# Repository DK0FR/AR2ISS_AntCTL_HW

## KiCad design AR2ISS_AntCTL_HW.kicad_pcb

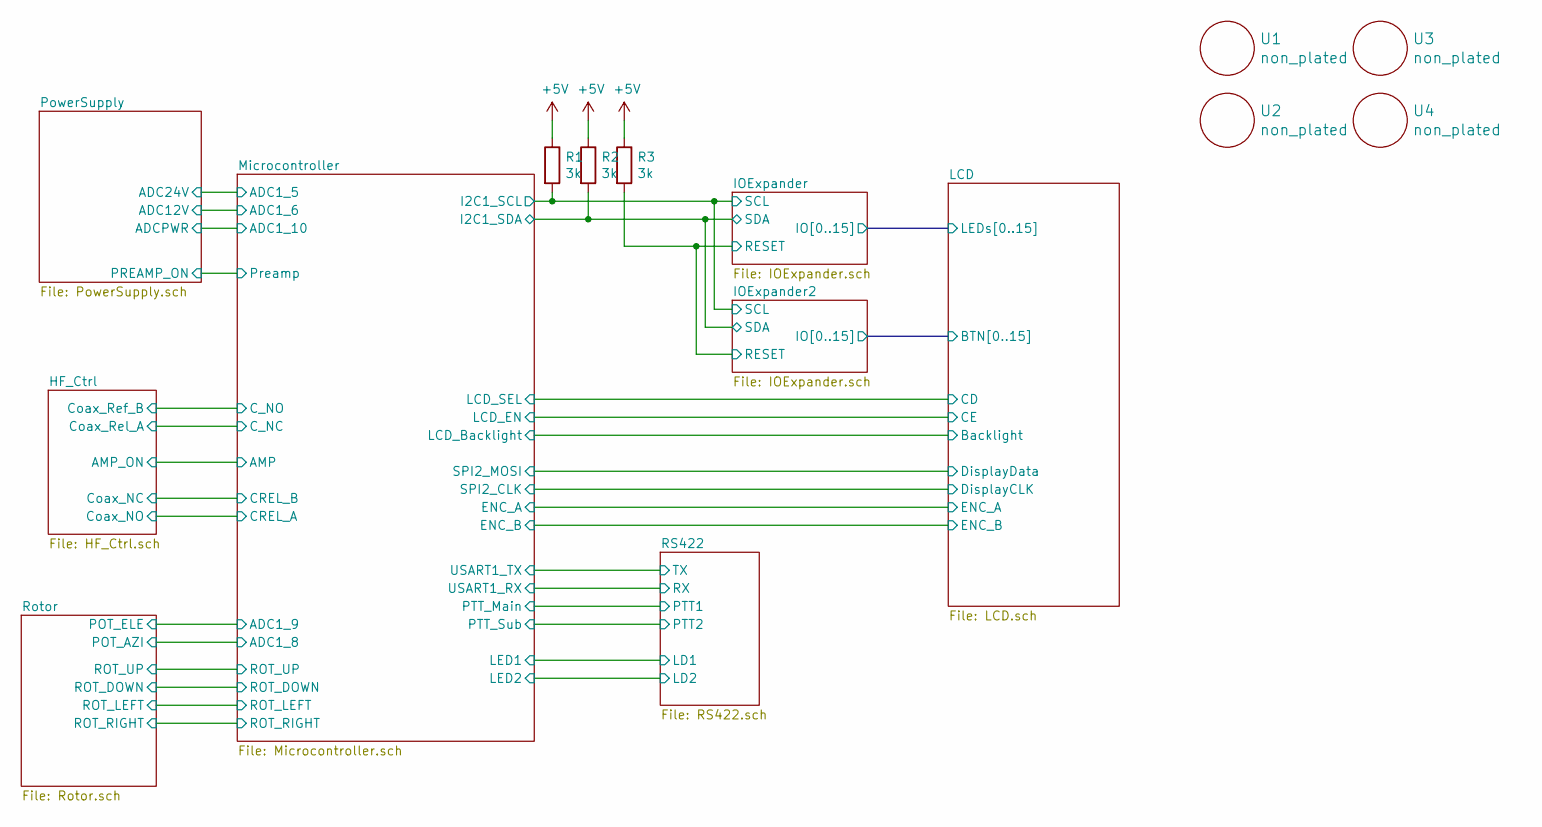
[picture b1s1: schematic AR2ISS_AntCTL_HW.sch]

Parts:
R1, R2, R3: 3k; R_0603_1608Metric
U1, U2, U3, U4: non_plated; non_plated_3mm

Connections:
+5V: R1.1, R2.1, R3.1; also elsewhere on the board
/IOExpander/RESET: R3.2; also elsewhere on the board
/Microcontroller/I2C1_SCL: R1.2; also elsewhere on the board
/Microcontroller/I2C1_SDA: R2.2; also elsewhere on the board

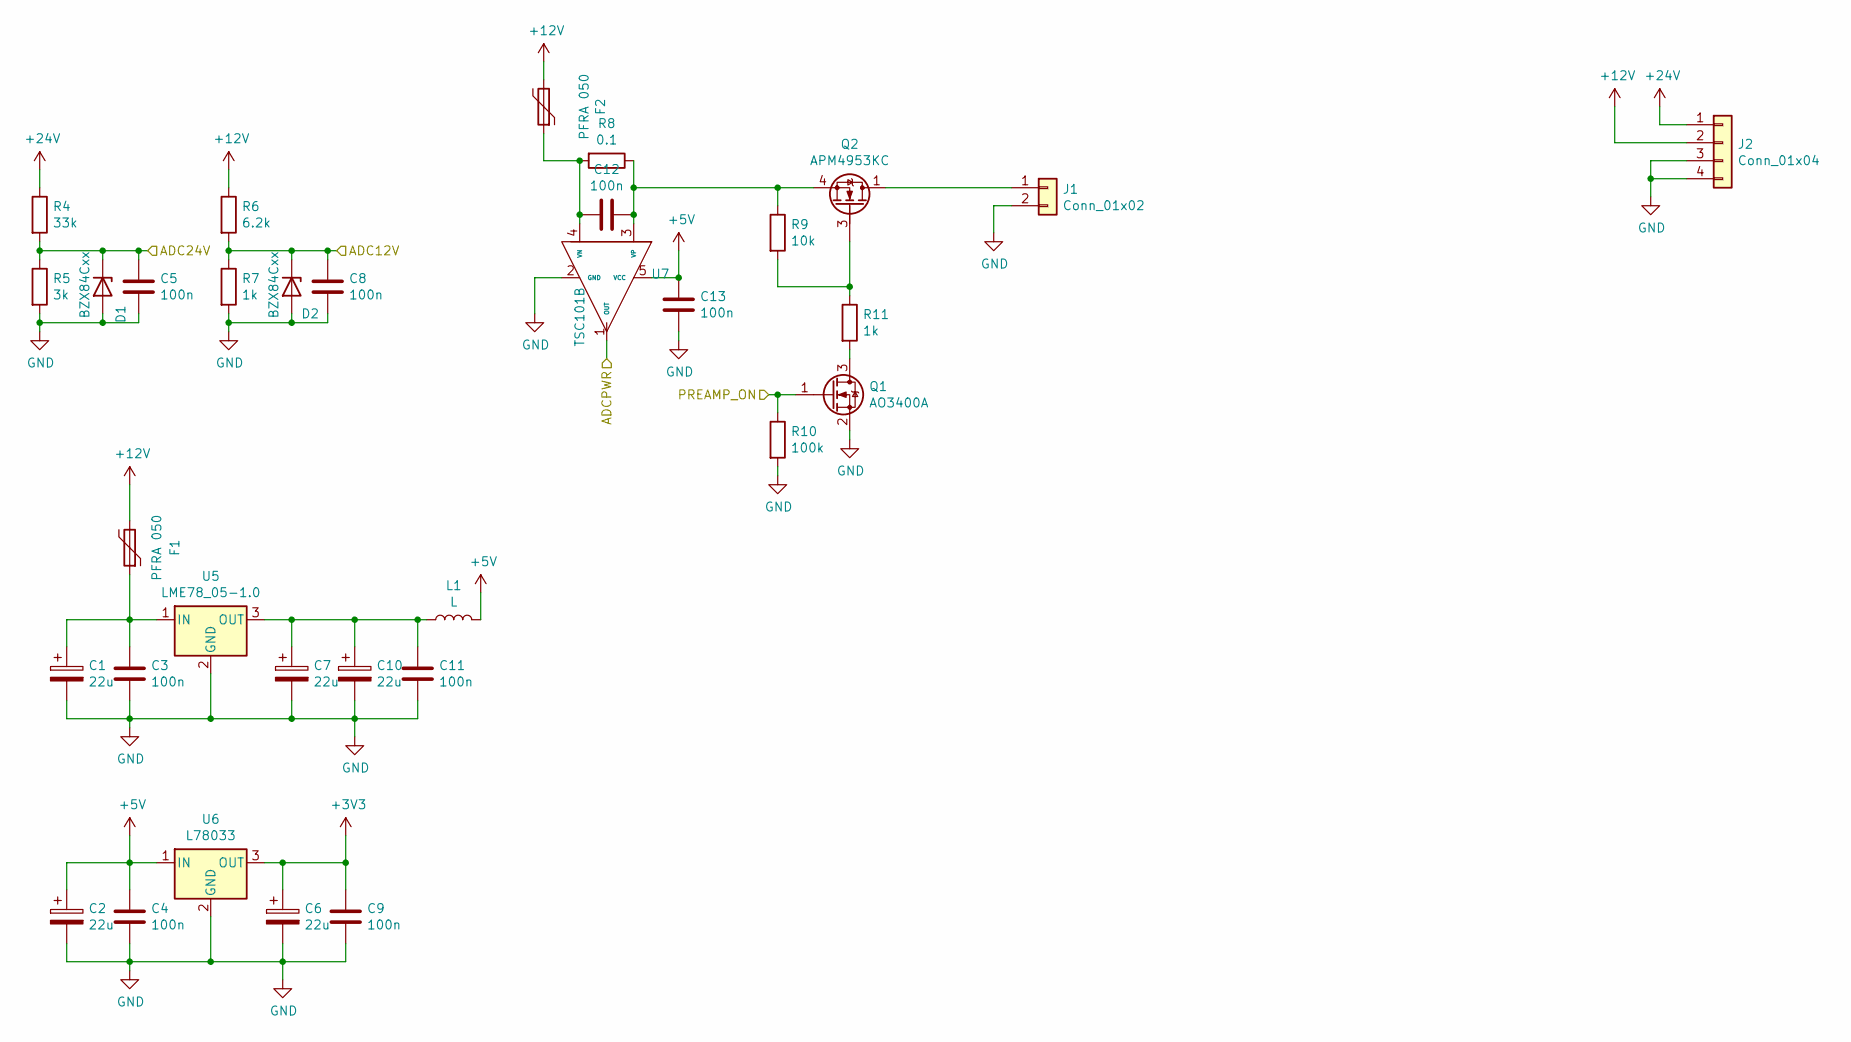
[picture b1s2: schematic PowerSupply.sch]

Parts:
C1, C2, C6, C7, C10: 22u; CP_Radial_D6.3mm_P2.50mm
C3, C4, C5, C8, C9, C11, C12, C13: 100n; C_0603_1608Metric
D1, D2: BZX84Cxx; D_SOT-23_ANK
F1, F2: PFRA 050; Fuse_BelFuse_0ZRE0005FF_L8.3mm_W3.8mm
J1: Conn_01x02; RM3.5_1x2
J2: Conn_01x04; 250-204
L1: L; L_0603_1608Metric
Q1: AO3400A; SOT-23
Q2: APM4953KC; SOT-363_SC-70-6_Handsoldering
R4: 33k; R_0603_1608Metric
R5: 3k; R_0603_1608Metric
R6: 6.2k; R_0603_1608Metric
R7, R11: 1k; R_0603_1608Metric
R8: 0.1; R_1206_3216Metric_Pad1.30x1.75mm_HandSolder
R9: 10k; R_0603_1608Metric
R10: 100k; R_0603_1608Metric
U5: LME78_05-1.0; TO-220-3_Vertical
U6: L78033; SOT-223
U7: TSC101B; SOT-23-5_HandSoldering

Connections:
+3V3: C6.1, C9.1, U6.3 (OUT); also elsewhere on the board
+5V: C2.1, C4.1, C13.1, L1.2, U6.1 (IN), U7.5 (VCC); also elsewhere on the board
+12V: F1.2, F2.2, J2.2, R6.1
+24V: J2.1, R4.1; also elsewhere on the board
/Microcontroller/ADC1_5: C5.1, D1.1 (K), R4.2, R5.1; also elsewhere on the board
/Microcontroller/ADC1_10: U7.1 (OUT); also elsewhere on the board
/PowerSupply/ADC12V: C8.1, D2.1 (K), R6.2, R7.1; also elsewhere on the board
/PowerSupply/PREAMP_ON: Q1.1 (G), R10.1; also elsewhere on the board
GND: C1.2, C2.2, C3.2, C4.2, C5.2, C6.2, C7.2, C8.2, C9.2, C10.2, C11.2, C13.2, D1.2 (A), D2.2 (A), J1.2, J2.3, J2.4, Q1.2 (S), R5.2, R7.2, R10.2, U5.2 (GND), U6.2 (GND), U7.2 (GND); also elsewhere on the board
unnamed: C1.1, C3.1, F1.1, U5.1 (IN)
unnamed: C7.1, C10.1, C11.1, L1.1, U5.3 (OUT)
unnamed: C12.1, F2.1, R8.2, U7.4 (VN)
unnamed: C12.2, Q2.4 (S), R8.1, R9.1, U7.3 (VP)
unnamed: J1.1, Q2.1 (D), Q2.2 (D), Q2.5 (D), Q2.6 (D)
unnamed: Q1.3 (D), R11.2
unnamed: Q2.3 (G), R9.2, R11.1

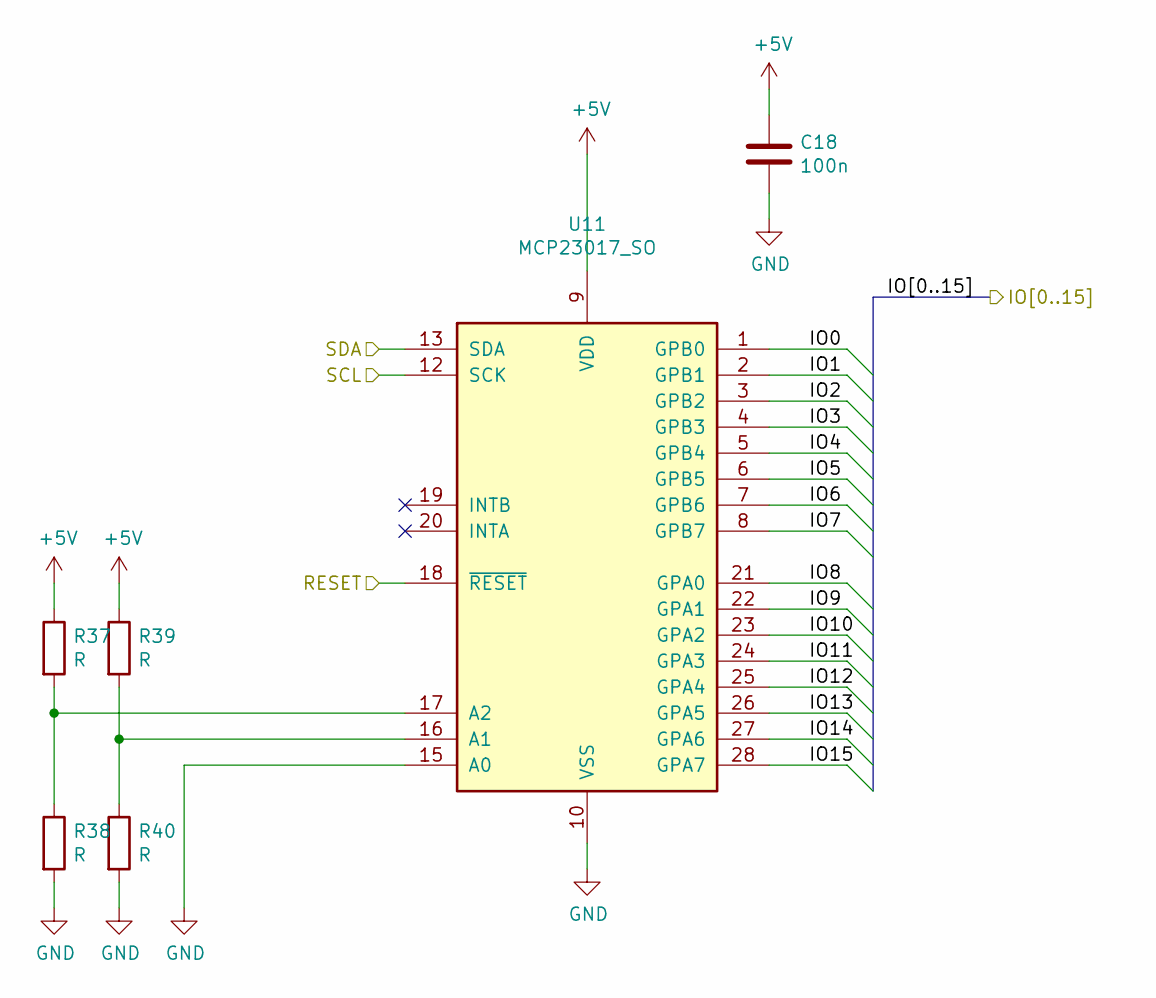
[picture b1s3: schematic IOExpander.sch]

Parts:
C18: 100n; C_0603_1608Metric
R12, R13, R14, R15: R; R_0603_1608Metric
U11: MCP23017_SO; SOIC-28W_7.5x17.9mm_P1.27mm

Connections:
+5V: C18.1, R12.1, R14.1, U11.9 (VDD); also elsewhere on the board
/IOExpander/IO0: U11.1 (GPB0); also elsewhere on the board
/IOExpander/IO1: U11.2 (GPB1); also elsewhere on the board
/IOExpander/IO2: U11.3 (GPB2); also elsewhere on the board
/IOExpander/IO3: U11.4 (GPB3); also elsewhere on the board
/IOExpander/IO4: U11.5 (GPB4); also elsewhere on the board
/IOExpander/IO5: U11.6 (GPB5); also elsewhere on the board
/IOExpander/IO6: U11.7 (GPB6); also elsewhere on the board
/IOExpander/IO7: U11.8 (GPB7); also elsewhere on the board
/IOExpander/IO8: U11.21 (GPA0); also elsewhere on the board
/IOExpander/IO9: U11.22 (GPA1); also elsewhere on the board
/IOExpander/IO10: U11.23 (GPA2); also elsewhere on the board
/IOExpander/IO11: U11.24 (GPA3); also elsewhere on the board
/IOExpander/IO12: U11.25 (GPA4); also elsewhere on the board
/IOExpander/IO13: U11.26 (GPA5); also elsewhere on the board
/IOExpander/IO14: U11.27 (GPA6); also elsewhere on the board
/IOExpander/IO15: U11.28 (GPA7)
/IOExpander/RESET: U11.18 (~RESET~); also elsewhere on the board
/Microcontroller/I2C1_SCL: U11.12 (SCK); also elsewhere on the board
/Microcontroller/I2C1_SDA: U11.13 (SDA); also elsewhere on the board
GND: C18.2, R13.2, R15.2, U11.10 (VSS), U11.15 (A0); also elsewhere on the board

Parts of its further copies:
C14: 100n; C_0603_1608Metric
R37, R38, R39, R40: R; R_0603_1608Metric
U8: MCP23017_SO; SOIC-28W_7.5x17.9mm_P1.27mm

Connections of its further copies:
+5V: C14.1, R37.1, R39.1, U8.9 (VDD); also elsewhere on the board
/IOExpander/RESET: U8.18 (~RESET~); also elsewhere on the board
/LCD/BTN0: U8.1 (GPB0); also elsewhere on the board
/LCD/BTN1: U8.2 (GPB1); also elsewhere on the board
/LCD/BTN2: U8.3 (GPB2); also elsewhere on the board
/LCD/BTN3: U8.4 (GPB3); also elsewhere on the board
/LCD/BTN4: U8.5 (GPB4); also elsewhere on the board
/LCD/BTN5: U8.6 (GPB5)
/LCD/BTN6: U8.7 (GPB6)
/LCD/BTN7: U8.8 (GPB7)
/LCD/BTN8: U8.21 (GPA0); also elsewhere on the board
/LCD/BTN9: U8.22 (GPA1); also elsewhere on the board
/LCD/BTN10: U8.23 (GPA2); also elsewhere on the board
/LCD/BTN11: U8.24 (GPA3); also elsewhere on the board
/LCD/BTN12: U8.25 (GPA4); also elsewhere on the board
/LCD/BTN13: U8.26 (GPA5)
/LCD/BTN14: U8.27 (GPA6)
/LCD/BTN15: U8.28 (GPA7)
/Microcontroller/I2C1_SCL: U8.12 (SCK); also elsewhere on the board
/Microcontroller/I2C1_SDA: U8.13 (SDA); also elsewhere on the board
GND: C14.2, R38.2, R40.2, U8.10 (VSS), U8.15 (A0); also elsewhere on the board

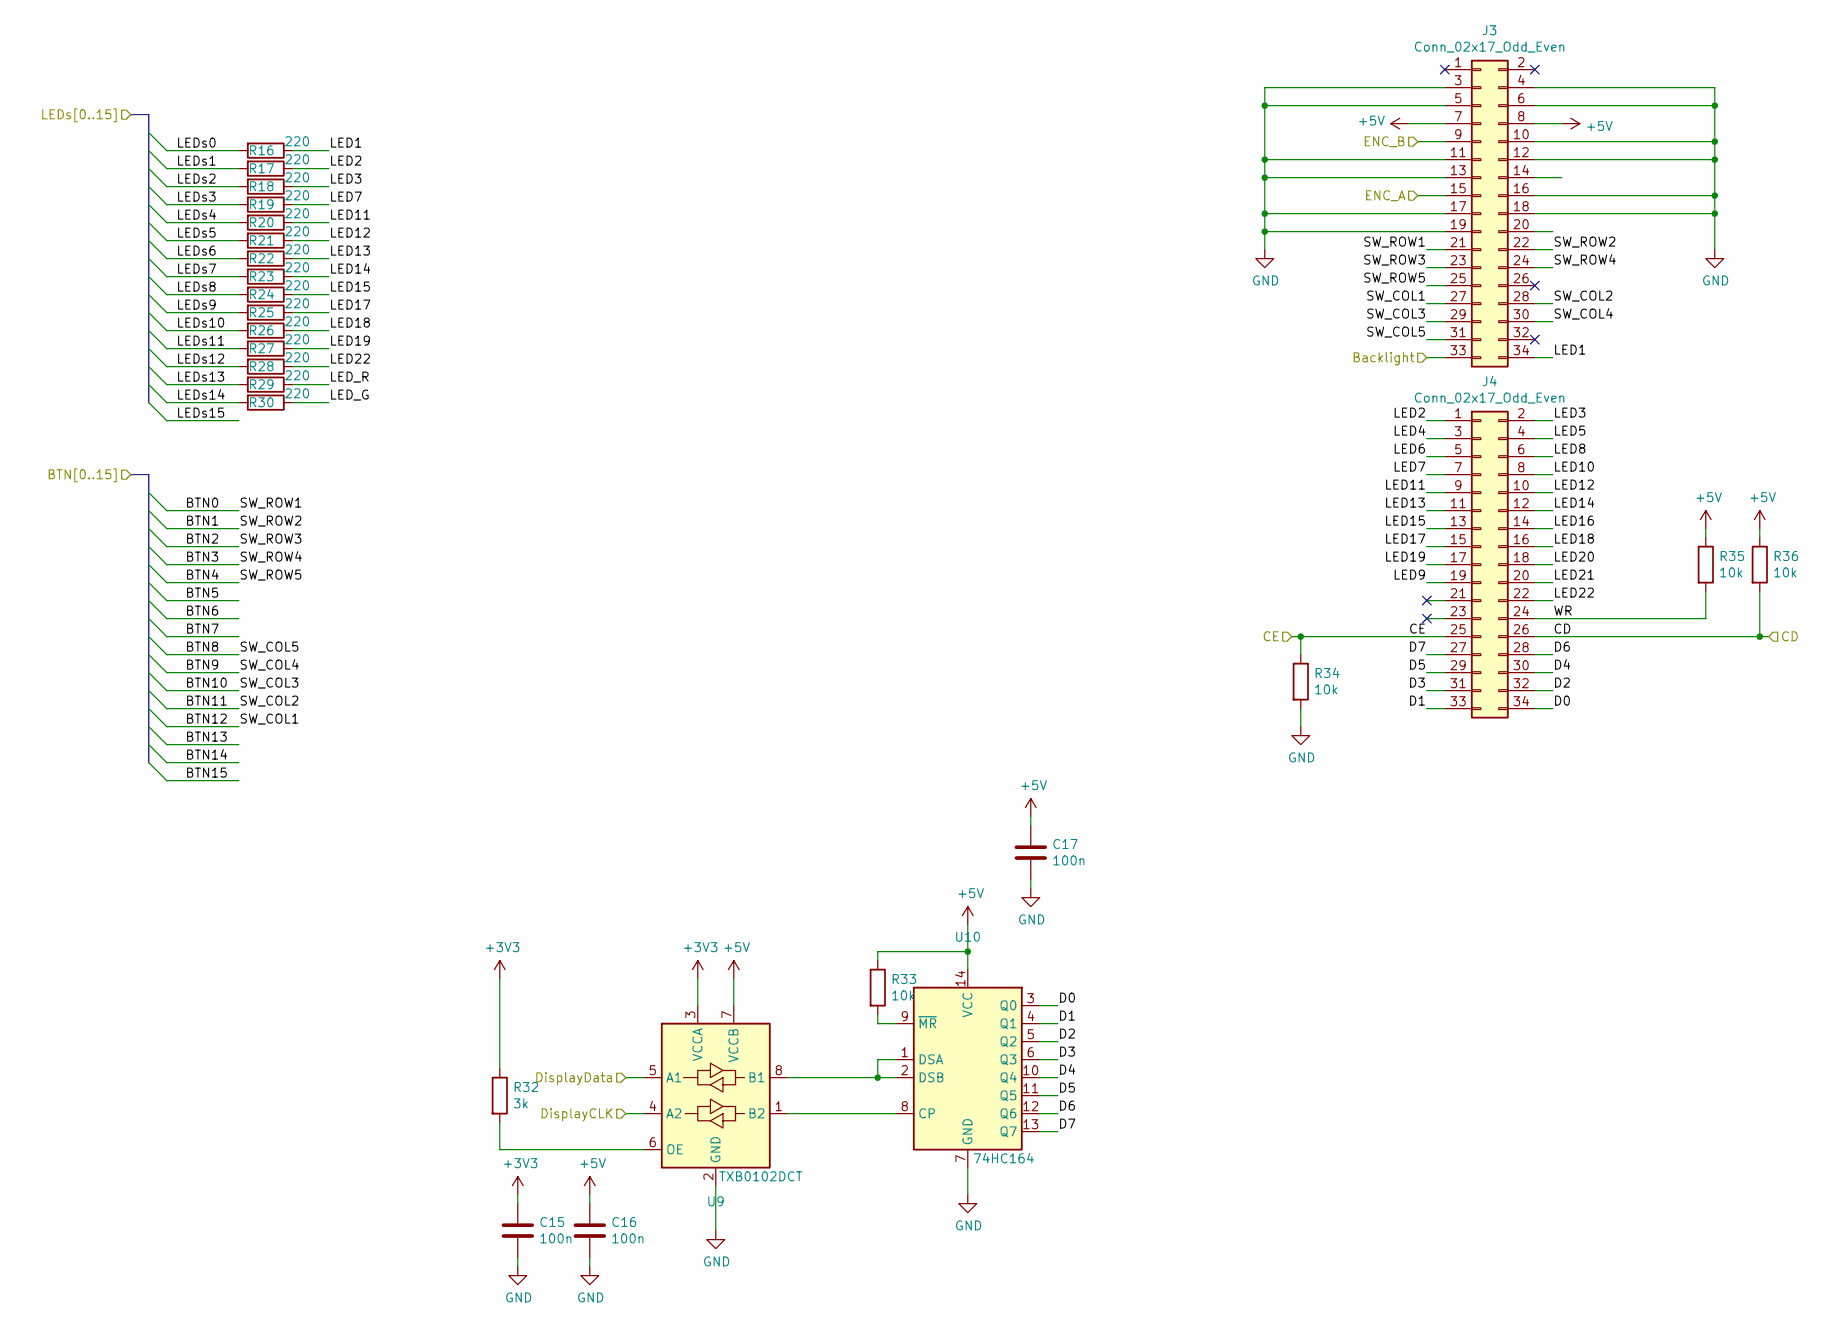
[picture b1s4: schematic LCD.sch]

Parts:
C15, C16, C17: 100n; C_0603_1608Metric
J3, J4: Conn_02x17_Odd_Even; IDC-Header_2x17_P2.54mm_Vertical
R16, R17, R18, R19, R20, R21, R22, R23, R24, R25, R26, R27, R28, R29, R30: 220; R_0603_1608Metric
R32: 3k; R_0603_1608Metric
R33, R34, R35, R36: 10k; R_0603_1608Metric
U9: TXB0102DCT; TSSOP-8_3x3mm_P0.65mm
U10: 74HC164; SOIC-14_3.9x8.7mm_P1.27mm

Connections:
+3V3: C15.1, R32.1, U9.3 (VCCA); also elsewhere on the board
+5V: C16.1, C17.1, J3.7, J3.8, R33.1, R35.1, R36.1, U9.7 (VCCB), U10.14 (VCC); also elsewhere on the board
/IOExpander/IO0: R16.2; also elsewhere on the board
/IOExpander/IO1: R17.2; also elsewhere on the board
/IOExpander/IO2: R18.2; also elsewhere on the board
/IOExpander/IO3: R19.2; also elsewhere on the board
/IOExpander/IO4: R20.2; also elsewhere on the board
/IOExpander/IO5: R21.2; also elsewhere on the board
/IOExpander/IO6: R22.2; also elsewhere on the board
/IOExpander/IO7: R23.2; also elsewhere on the board
/IOExpander/IO8: R24.2; also elsewhere on the board
/IOExpander/IO9: R25.2; also elsewhere on the board
/IOExpander/IO10: R26.2; also elsewhere on the board
/IOExpander/IO11: R27.2; also elsewhere on the board
/IOExpander/IO12: R28.2; also elsewhere on the board
/IOExpander/IO13: R29.2; also elsewhere on the board
/IOExpander/IO14: R30.2; also elsewhere on the board
/LCD/BTN0: J3.21; also elsewhere on the board
/LCD/BTN1: J3.22; also elsewhere on the board
/LCD/BTN2: J3.23; also elsewhere on the board
/LCD/BTN3: J3.24; also elsewhere on the board
/LCD/BTN4: J3.25; also elsewhere on the board
/LCD/BTN8: J3.31; also elsewhere on the board
/LCD/BTN9: J3.30; also elsewhere on the board
/LCD/BTN10: J3.29; also elsewhere on the board
/LCD/BTN11: J3.28; also elsewhere on the board
/LCD/BTN12: J3.27; also elsewhere on the board
/LCD/Backlight: J3.33; also elsewhere on the board
/LCD/CD: J4.26, R36.2; also elsewhere on the board
/LCD/CE: J4.25, R34.1; also elsewhere on the board
/LCD/D0: J4.34, U10.3 (Q0)
/LCD/D1: J4.33, U10.4 (Q1)
/LCD/D2: J4.32, U10.5 (Q2)
/LCD/D3: J4.31, U10.6 (Q3)
/LCD/D4: J4.30, U10.10 (Q4)
/LCD/D5: J4.29, U10.11 (Q5)
/LCD/D6: J4.28, U10.12 (Q6)
/LCD/D7: J4.27, U10.13 (Q7)
/LCD/DisplayCLK: U9.4 (A2); also elsewhere on the board
/LCD/DisplayData: U9.5 (A1); also elsewhere on the board
/LCD/ENC_A: J3.15; also elsewhere on the board
/LCD/ENC_B: J3.9; also elsewhere on the board
/LCD/LED1: J3.34, R16.1
/LCD/LED2: J4.1, R17.1
/LCD/LED3: J4.2, R18.1
/LCD/LED4: J4.3
/LCD/LED5: J4.4
/LCD/LED6: J4.5
/LCD/LED7: J4.7, R19.1
/LCD/LED8: J4.6
/LCD/LED9: J4.19
/LCD/LED10: J4.8
/LCD/LED11: J4.9, R20.1
/LCD/LED12: J4.10, R21.1
/LCD/LED13: J4.11, R22.1
/LCD/LED14: J4.12, R23.1
/LCD/LED15: J4.13, R24.1
/LCD/LED16: J4.14
/LCD/LED17: J4.15, R25.1
/LCD/LED18: J4.16, R26.1
/LCD/LED19: J4.17, R27.1
/LCD/LED20: J4.18
/LCD/LED21: J4.20
/LCD/LED22: J4.22, R28.1
/LCD/LED_G: R30.1
/LCD/LED_R: R29.1
/LCD/WR: J4.24, R35.2
GND: C15.2, C16.2, C17.2, J3.3, J3.4, J3.5, J3.6, J3.10, J3.11, J3.12, J3.13, J3.16, J3.17, J3.18, J3.19, R34.2, U9.2 (GND), U10.7 (GND); also elsewhere on the board
unnamed: R32.2, U9.6 (OE)
unnamed: R33.2, U10.9 (~MR)
unnamed: U9.8 (B1), U10.1 (DSA), U10.2 (DSB)
unnamed: U9.1 (B2), U10.8 (CP)

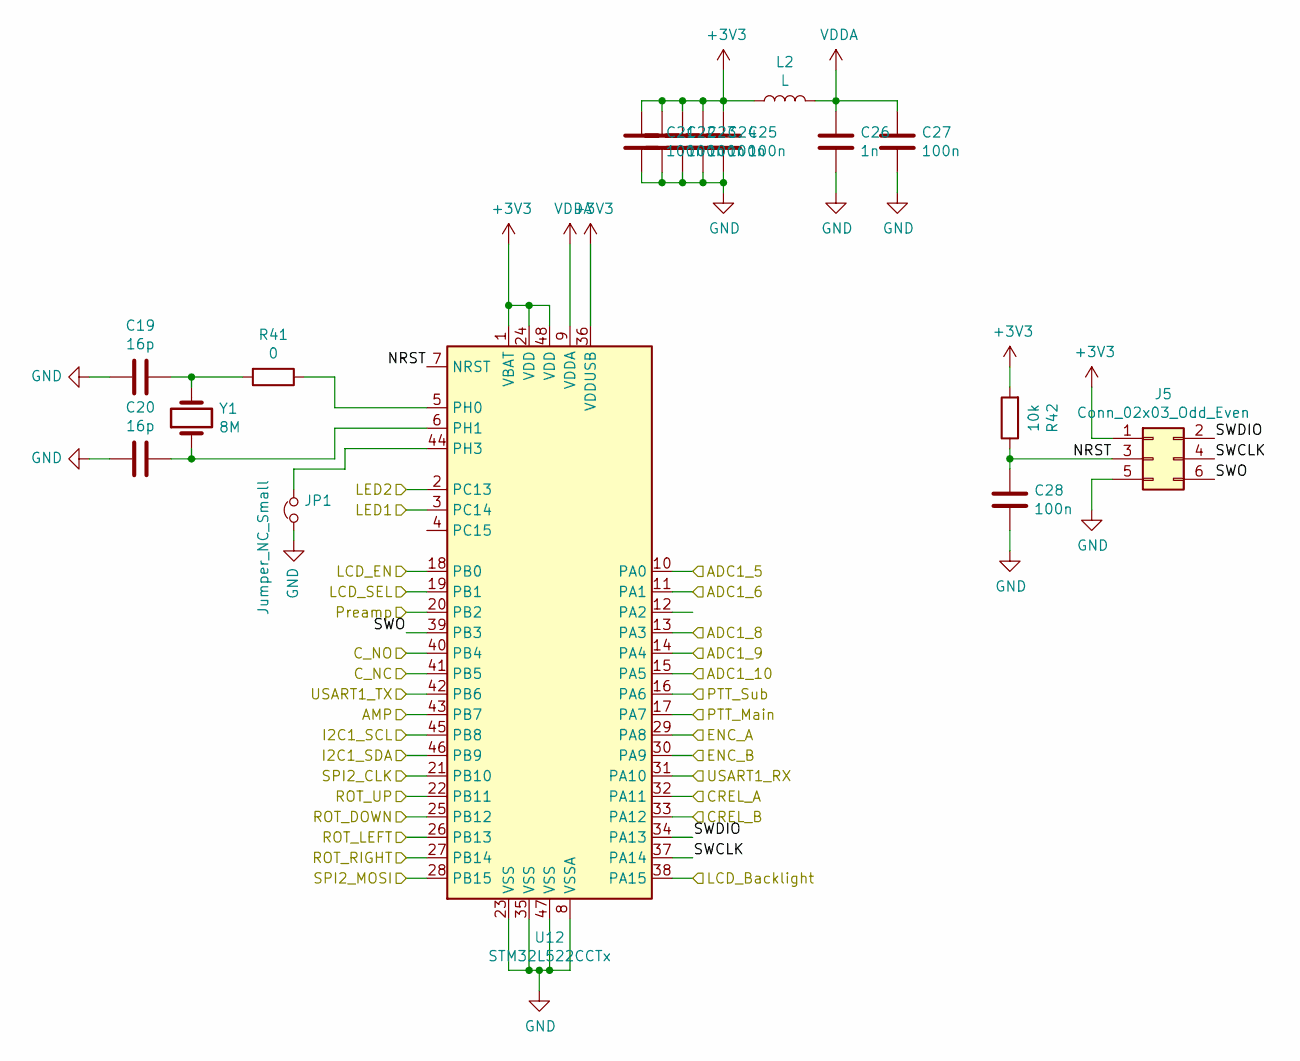
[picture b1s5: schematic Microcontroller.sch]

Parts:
C19, C20: 16p; C_0603_1608Metric
C21, C22, C23, C24, C25, C27, C28: 100n; C_0603_1608Metric
C26: 1n; C_0603_1608Metric
J5: Conn_02x03_Odd_Even; IDC-Header_2x03_P2.54mm_Vertical
JP1: Jumper_NC_Small; SolderJumper-2_P1.3mm_Bridged_RoundedPad1.0x1.5mm
L2: L; L_0603_1608Metric
R41: 0; R_0603_1608Metric
R42: 10k; R_0603_1608Metric
U12: STM32L522CCTx; LQFP-48_7x7mm_P0.5mm
Y1: 8M; Crystal_SMD_5032-2Pin_5.0x3.2mm_HandSoldering

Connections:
+3V3: C21.2, C22.2, C23.2, C24.2, C25.2, J5.1, L2.1, R42.2, U12.1 (VBAT), U12.24 (VDD), U12.36 (VDDUSB), U12.48 (VDD); also elsewhere on the board
/LCD/Backlight: U12.38 (PA15); also elsewhere on the board
/LCD/CD: U12.19 (PB1); also elsewhere on the board
/LCD/CE: U12.18 (PB0); also elsewhere on the board
/LCD/DisplayCLK: U12.21 (PB10); also elsewhere on the board
/LCD/DisplayData: U12.28 (PB15); also elsewhere on the board
/LCD/ENC_A: U12.29 (PA8); also elsewhere on the board
/LCD/ENC_B: U12.30 (PA9); also elsewhere on the board
/Microcontroller/ADC1_5: U12.10 (PA0); also elsewhere on the board
/Microcontroller/ADC1_8: U12.13 (PA3); also elsewhere on the board
/Microcontroller/ADC1_9: U12.14 (PA4); also elsewhere on the board
/Microcontroller/ADC1_10: U12.15 (PA5); also elsewhere on the board
/Microcontroller/AMP: U12.43 (PB7); also elsewhere on the board
/Microcontroller/CREL_A: U12.32 (PA11); also elsewhere on the board
/Microcontroller/CREL_B: U12.33 (PA12); also elsewhere on the board
/Microcontroller/C_NC: U12.41 (PB5); also elsewhere on the board
/Microcontroller/C_NO: U12.40 (PB4); also elsewhere on the board
/Microcontroller/I2C1_SCL: U12.45 (PB8); also elsewhere on the board
/Microcontroller/I2C1_SDA: U12.46 (PB9); also elsewhere on the board
/Microcontroller/NRST: C28.2, J5.3, R42.1, U12.7 (NRST)
/Microcontroller/ROT_DOWN: U12.25 (PB12); also elsewhere on the board
/Microcontroller/ROT_LEFT: U12.26 (PB13); also elsewhere on the board
/Microcontroller/ROT_RIGHT: U12.27 (PB14); also elsewhere on the board
/Microcontroller/ROT_UP: U12.22 (PB11); also elsewhere on the board
/Microcontroller/SWCLK: J5.4, U12.37 (PA14)
/Microcontroller/SWDIO: J5.2, U12.34 (PA13)
/Microcontroller/SWO: J5.6, U12.39 (PB3)
/PowerSupply/ADC12V: U12.11 (PA1); also elsewhere on the board
/PowerSupply/PREAMP_ON: U12.20 (PB2); also elsewhere on the board
/RS422/LD1: U12.3 (PC14); also elsewhere on the board
/RS422/LD2: U12.2 (PC13); also elsewhere on the board
/RS422/PTT1: U12.17 (PA7); also elsewhere on the board
/RS422/PTT2: U12.16 (PA6); also elsewhere on the board
/RS422/RX: U12.31 (PA10); also elsewhere on the board
/RS422/TX: U12.42 (PB6); also elsewhere on the board
GND: C19.2, C20.2, C21.1, C22.1, C23.1, C24.1, C25.1, C26.1, C27.1, C28.1, J5.5, JP1.1, U12.8 (VSSA), U12.23 (VSS), U12.35 (VSS), U12.47 (VSS); also elsewhere on the board
unnamed: C19.1, R41.2, Y1.2
unnamed: C20.1, U12.6 (PH1), Y1.1
unnamed: JP1.2, U12.44 (PH3)
unnamed: R41.1, U12.5 (PH0)
VDDA: C26.2, C27.2, L2.2, U12.9 (VDDA)

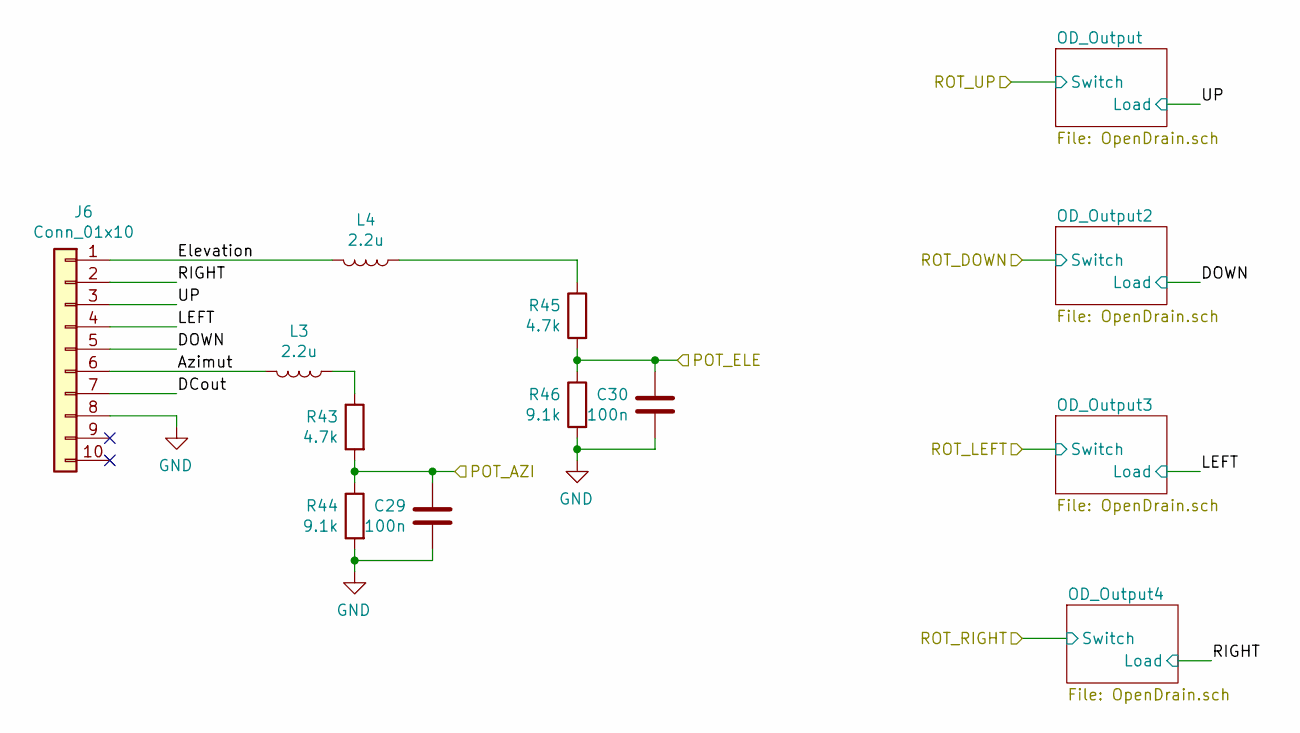
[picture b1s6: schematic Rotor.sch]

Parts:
C29, C30: 100n; C_0603_1608Metric
J6: Conn_01x10; PinHeader_2x05_P2.54mm_Vertical
L3, L4: 2.2u; L_0603_1608Metric
R43, R45: 4.7k; R_0603_1608Metric
R44, R46: 9.1k; R_0603_1608Metric

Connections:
/Microcontroller/ADC1_8: C29.1, R43.2, R44.1; also elsewhere on the board
/Microcontroller/ADC1_9: C30.1, R45.2, R46.1; also elsewhere on the board
/Rotor/Azimut: J6.6, L3.2
/Rotor/DCout: J6.7
/Rotor/DOWN: J6.5; also elsewhere on the board
/Rotor/Elevation: J6.1, L4.2
/Rotor/LEFT: J6.4; also elsewhere on the board
/Rotor/RIGHT: J6.2; also elsewhere on the board
/Rotor/UP: J6.3; also elsewhere on the board
GND: C29.2, C30.2, J6.8, R44.2, R46.2; also elsewhere on the board
unnamed: L3.1, R43.1
unnamed: L4.1, R45.1

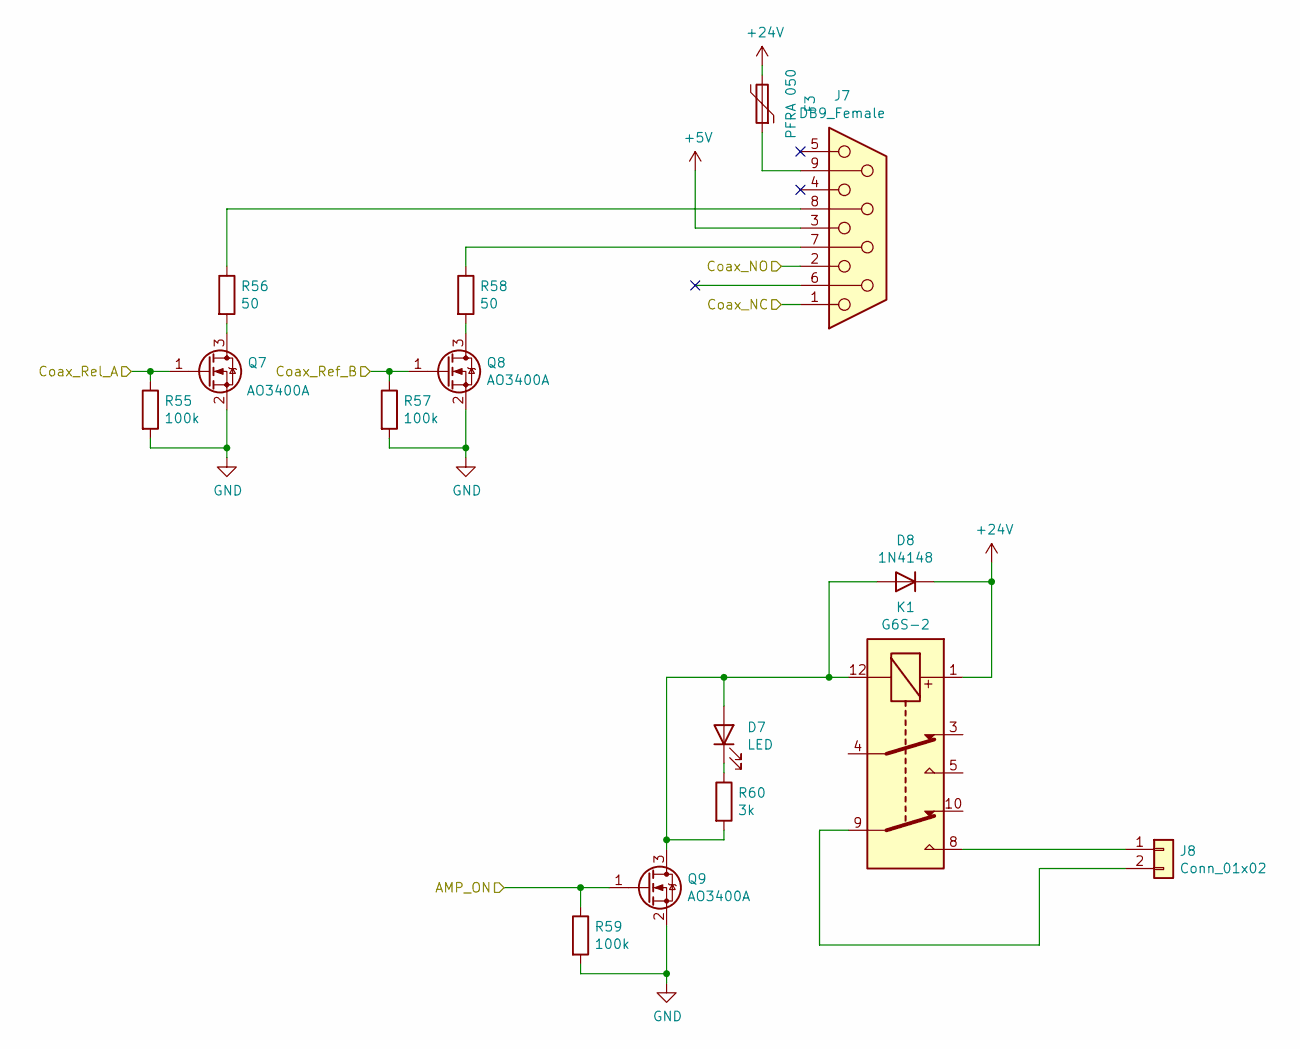
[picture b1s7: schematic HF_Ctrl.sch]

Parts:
D7: LED; D_0603_1608Metric
D8: 1N4148; D_DO-35_SOD27_P7.62mm_Horizontal
F3: PFRA 050; Fuse_BelFuse_0ZRE0005FF_L8.3mm_W3.8mm
J7: DB9_Female; DSUB-9_Female_Vertical_P2.77x2.84mm
J8: Conn_01x02; RM3.5_1x2
K1: G6S-2; Relay_DPDT_Omron_G6S-2
Q7, Q8, Q9: AO3400A; SOT-23
R55, R57, R59: 100k; R_0603_1608Metric
R56, R58: 50; R_1206_3216Metric_Pad1.30x1.75mm_HandSolder
R60: 3k; R_0603_1608Metric

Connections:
+5V: J7.3; also elsewhere on the board
+24V: D8.1 (K), F3.2, K1.1; also elsewhere on the board
/Microcontroller/AMP: Q9.1 (G), R59.1; also elsewhere on the board
/Microcontroller/CREL_A: J7.2; also elsewhere on the board
/Microcontroller/CREL_B: J7.1; also elsewhere on the board
/Microcontroller/C_NC: Q7.1 (G), R55.1; also elsewhere on the board
/Microcontroller/C_NO: Q8.1 (G), R57.1; also elsewhere on the board
GND: Q7.2 (S), Q8.2 (S), Q9.2 (S), R55.2, R57.2, R59.2; also elsewhere on the board
unnamed: D7.1 (K), R60.1
unnamed: D7.2 (A), D8.2 (A), K1.12, Q9.3 (D), R60.2
unnamed: F3.1, J7.9
unnamed: J7.7, R58.1
unnamed: J7.8, R56.1
unnamed: J8.1, K1.8
unnamed: J8.2, K1.9
unnamed: Q7.3 (D), R56.2
unnamed: Q8.3 (D), R58.2

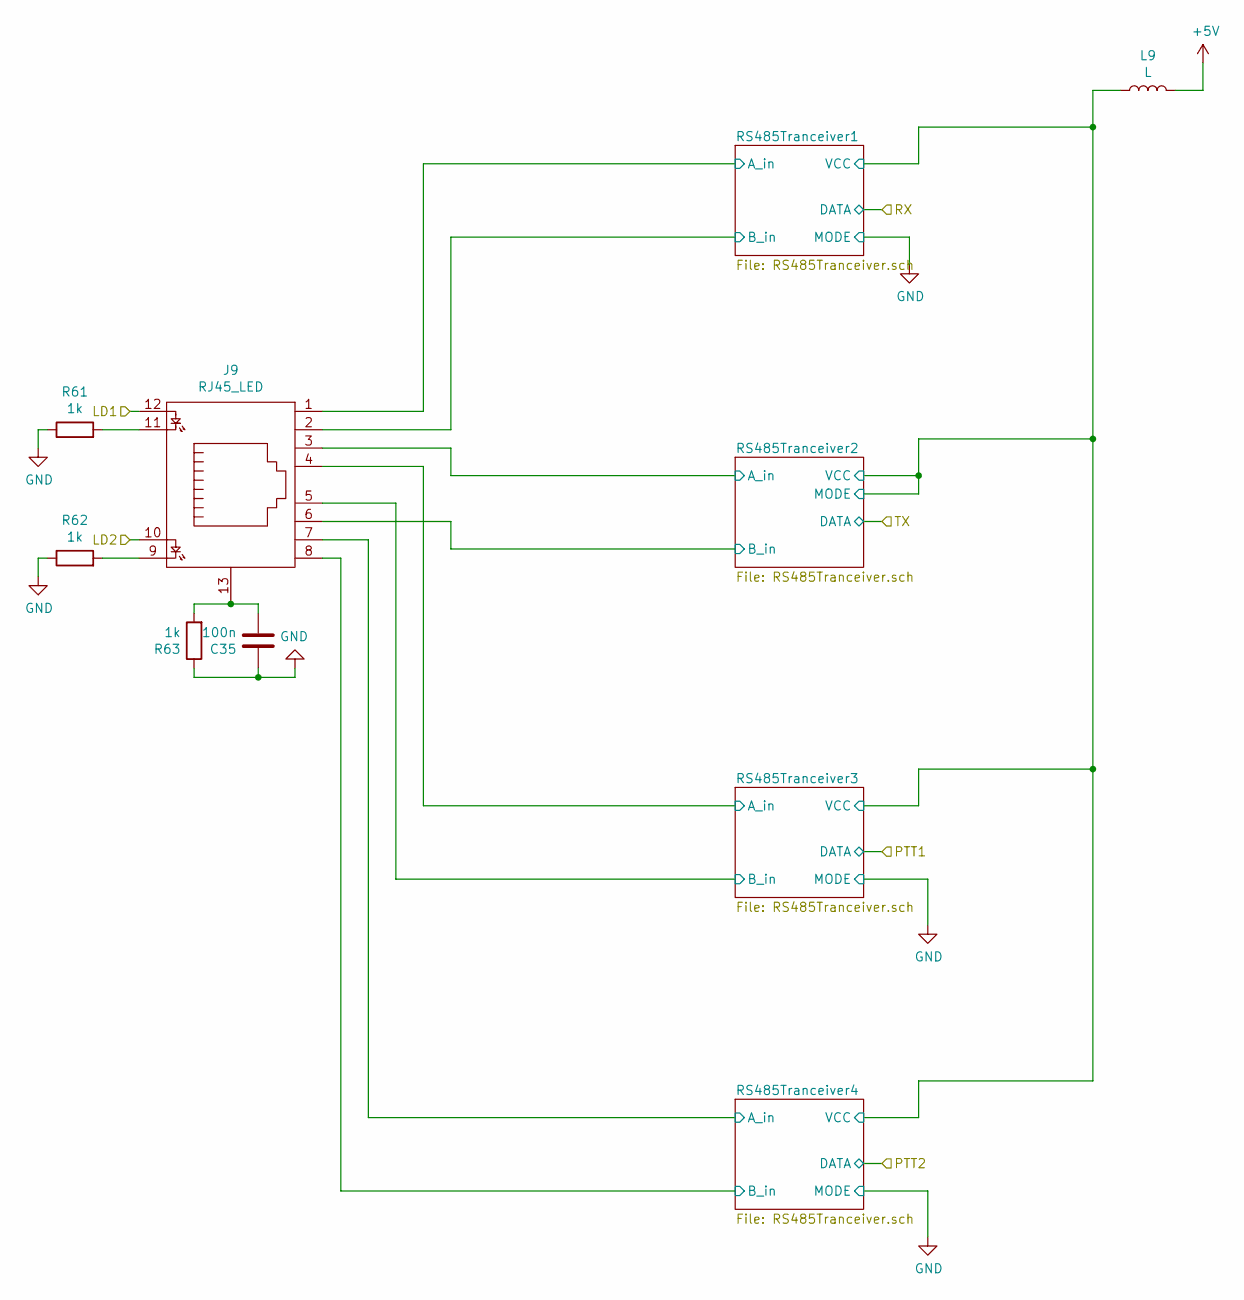
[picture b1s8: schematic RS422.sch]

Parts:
C35: 100n; C_0603_1608Metric
J9: RJ45_LED
L9: L; L_0603_1608Metric
R61, R62, R63: 1k; R_0603_1608Metric

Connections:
+5V: L9.2; also elsewhere on the board
/RS422/LD1: J9.12; also elsewhere on the board
/RS422/LD2: J9.10; also elsewhere on the board
/RS422/RS485Tranceiver1/A_in: J9.1; also elsewhere on the board
/RS422/RS485Tranceiver1/B_in: J9.2; also elsewhere on the board
/RS422/RS485Tranceiver2/A_in: J9.3; also elsewhere on the board
/RS422/RS485Tranceiver2/B_in: J9.6; also elsewhere on the board
/RS422/RS485Tranceiver2/MODE: L9.1; also elsewhere on the board
/RS422/RS485Tranceiver3/A_in: J9.4; also elsewhere on the board
/RS422/RS485Tranceiver3/B_in: J9.5; also elsewhere on the board
/RS422/RS485Tranceiver4/A_in: J9.7; also elsewhere on the board
/RS422/RS485Tranceiver4/B_in: J9.8; also elsewhere on the board
GND: C35.1, R61.1, R62.1, R63.1; also elsewhere on the board
unnamed: C35.2, J9.13, R63.2
unnamed: J9.9, R62.2
unnamed: J9.11, R61.2

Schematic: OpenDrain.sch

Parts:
C31: 1n; C_0603_1608Metric
D3: LED; D_0603_1608Metric
L5: 2.2u; L_0603_1608Metric
Q3: AO3400A; SOT-23
R47: 100k; R_0603_1608Metric
R48: 220; R_0603_1608Metric

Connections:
+5V: R48.1; also elsewhere on the board
/Microcontroller/ROT_UP: Q3.1 (G), R47.1; also elsewhere on the board
/Rotor/UP: L5.1; also elsewhere on the board
GND: C31.2, Q3.2 (S), R47.2; also elsewhere on the board
unnamed: C31.1, D3.1 (K), L5.2, Q3.3 (D)
unnamed: D3.2 (A), R48.2

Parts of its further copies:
C32, C33, C34: 1n; C_0603_1608Metric
D4, D5, D6: LED; D_0603_1608Metric
L6, L7, L8: 2.2u; L_0603_1608Metric
Q4, Q5, Q6: AO3400A; SOT-23
R49, R51, R53: 100k; R_0603_1608Metric
R50, R52, R54: 220; R_0603_1608Metric

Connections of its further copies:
+5V: R50.1, R52.1, R54.1; also elsewhere on the board
/Microcontroller/ROT_DOWN: Q4.1 (G), R49.1; also elsewhere on the board
/Microcontroller/ROT_LEFT: Q5.1 (G), R51.1; also elsewhere on the board
/Microcontroller/ROT_RIGHT: Q6.1 (G), R53.1; also elsewhere on the board
/Rotor/DOWN: L6.1; also elsewhere on the board
/Rotor/LEFT: L7.1; also elsewhere on the board
/Rotor/RIGHT: L8.1; also elsewhere on the board
GND: C32.2, C33.2, C34.2, Q4.2 (S), Q5.2 (S), Q6.2 (S), R49.2, R51.2, R53.2; also elsewhere on the board
unnamed: C32.1, D4.1 (K), L6.2, Q4.3 (D)
unnamed: C33.1, D5.1 (K), L7.2, Q5.3 (D)
unnamed: C34.1, D6.1 (K), L8.2, Q6.3 (D)
unnamed: D4.2 (A), R50.2
unnamed: D5.2 (A), R52.2
unnamed: D6.2 (A), R54.2

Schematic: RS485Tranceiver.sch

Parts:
C40: 100n; C_0603_1608Metric
R67, R68, R69: NB; R_0603_1608Metric
R70: 3k; R_0603_1608Metric
U13: SN65HVD3082; SOIC-8_3.9x4.9mm_P1.27mm

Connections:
/RS422/RS485Tranceiver1/DE1: R70.2, U13.2 (~RE~), U13.3 (DE)
/RS422/RS485Tranceiver1/filter/A_Out: R67.2, R68.1, U13.6 (A); also elsewhere on the board
/RS422/RS485Tranceiver1/filter/B_Out: R68.2, R69.1, U13.7 (B); also elsewhere on the board
/RS422/RS485Tranceiver2/MODE: C40.1, R67.1, U13.8 (VCC); also elsewhere on the board
/RS422/RX: U13.1 (RO), U13.4 (DI); also elsewhere on the board
GND: C40.2, R69.2, R70.1, U13.5 (GND); also elsewhere on the board

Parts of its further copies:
C45, C50, C55: 100n; C_0603_1608Metric
R74, R75, R76, R81, R82, R83, R88, R89, R90: NB; R_0603_1608Metric
R77, R84, R91: 3k; R_0603_1608Metric
U14, U15, U16: SN65HVD3082; SOIC-8_3.9x4.9mm_P1.27mm

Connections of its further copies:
/RS422/PTT1: U14.1 (RO), U14.4 (DI); also elsewhere on the board
/RS422/PTT2: U15.1 (RO), U15.4 (DI); also elsewhere on the board
/RS422/RS485Tranceiver2/DE1: R91.2, U16.2 (~RE~), U16.3 (DE)
/RS422/RS485Tranceiver2/MODE: C45.1, C50.1, C55.1, R74.1, R81.1, R88.1, R91.1, U14.8 (VCC), U15.8 (VCC), U16.8 (VCC); also elsewhere on the board
/RS422/RS485Tranceiver2/filter/A_Out: R88.2, R89.1, U16.6 (A); also elsewhere on the board
/RS422/RS485Tranceiver2/filter/B_Out: R89.2, R90.1, U16.7 (B); also elsewhere on the board
/RS422/RS485Tranceiver3/DE1: R77.2, U14.2 (~RE~), U14.3 (DE)
/RS422/RS485Tranceiver3/filter/A_Out: R74.2, R75.1, U14.6 (A); also elsewhere on the board
/RS422/RS485Tranceiver3/filter/B_Out: R75.2, R76.1, U14.7 (B); also elsewhere on the board
/RS422/RS485Tranceiver4/DE1: R84.2, U15.2 (~RE~), U15.3 (DE)
/RS422/RS485Tranceiver4/filter/A_Out: R81.2, R82.1, U15.6 (A); also elsewhere on the board
/RS422/RS485Tranceiver4/filter/B_Out: R82.2, R83.1, U15.7 (B); also elsewhere on the board
/RS422/TX: U16.1 (RO), U16.4 (DI); also elsewhere on the board
GND: C45.2, C50.2, C55.2, R76.2, R77.1, R83.2, R84.1, R90.2, U14.5 (GND), U15.5 (GND), U16.5 (GND); also elsewhere on the board

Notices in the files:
parts and their libraries:
Copyright 2016 Accelerated Designs. All rights reserved.
